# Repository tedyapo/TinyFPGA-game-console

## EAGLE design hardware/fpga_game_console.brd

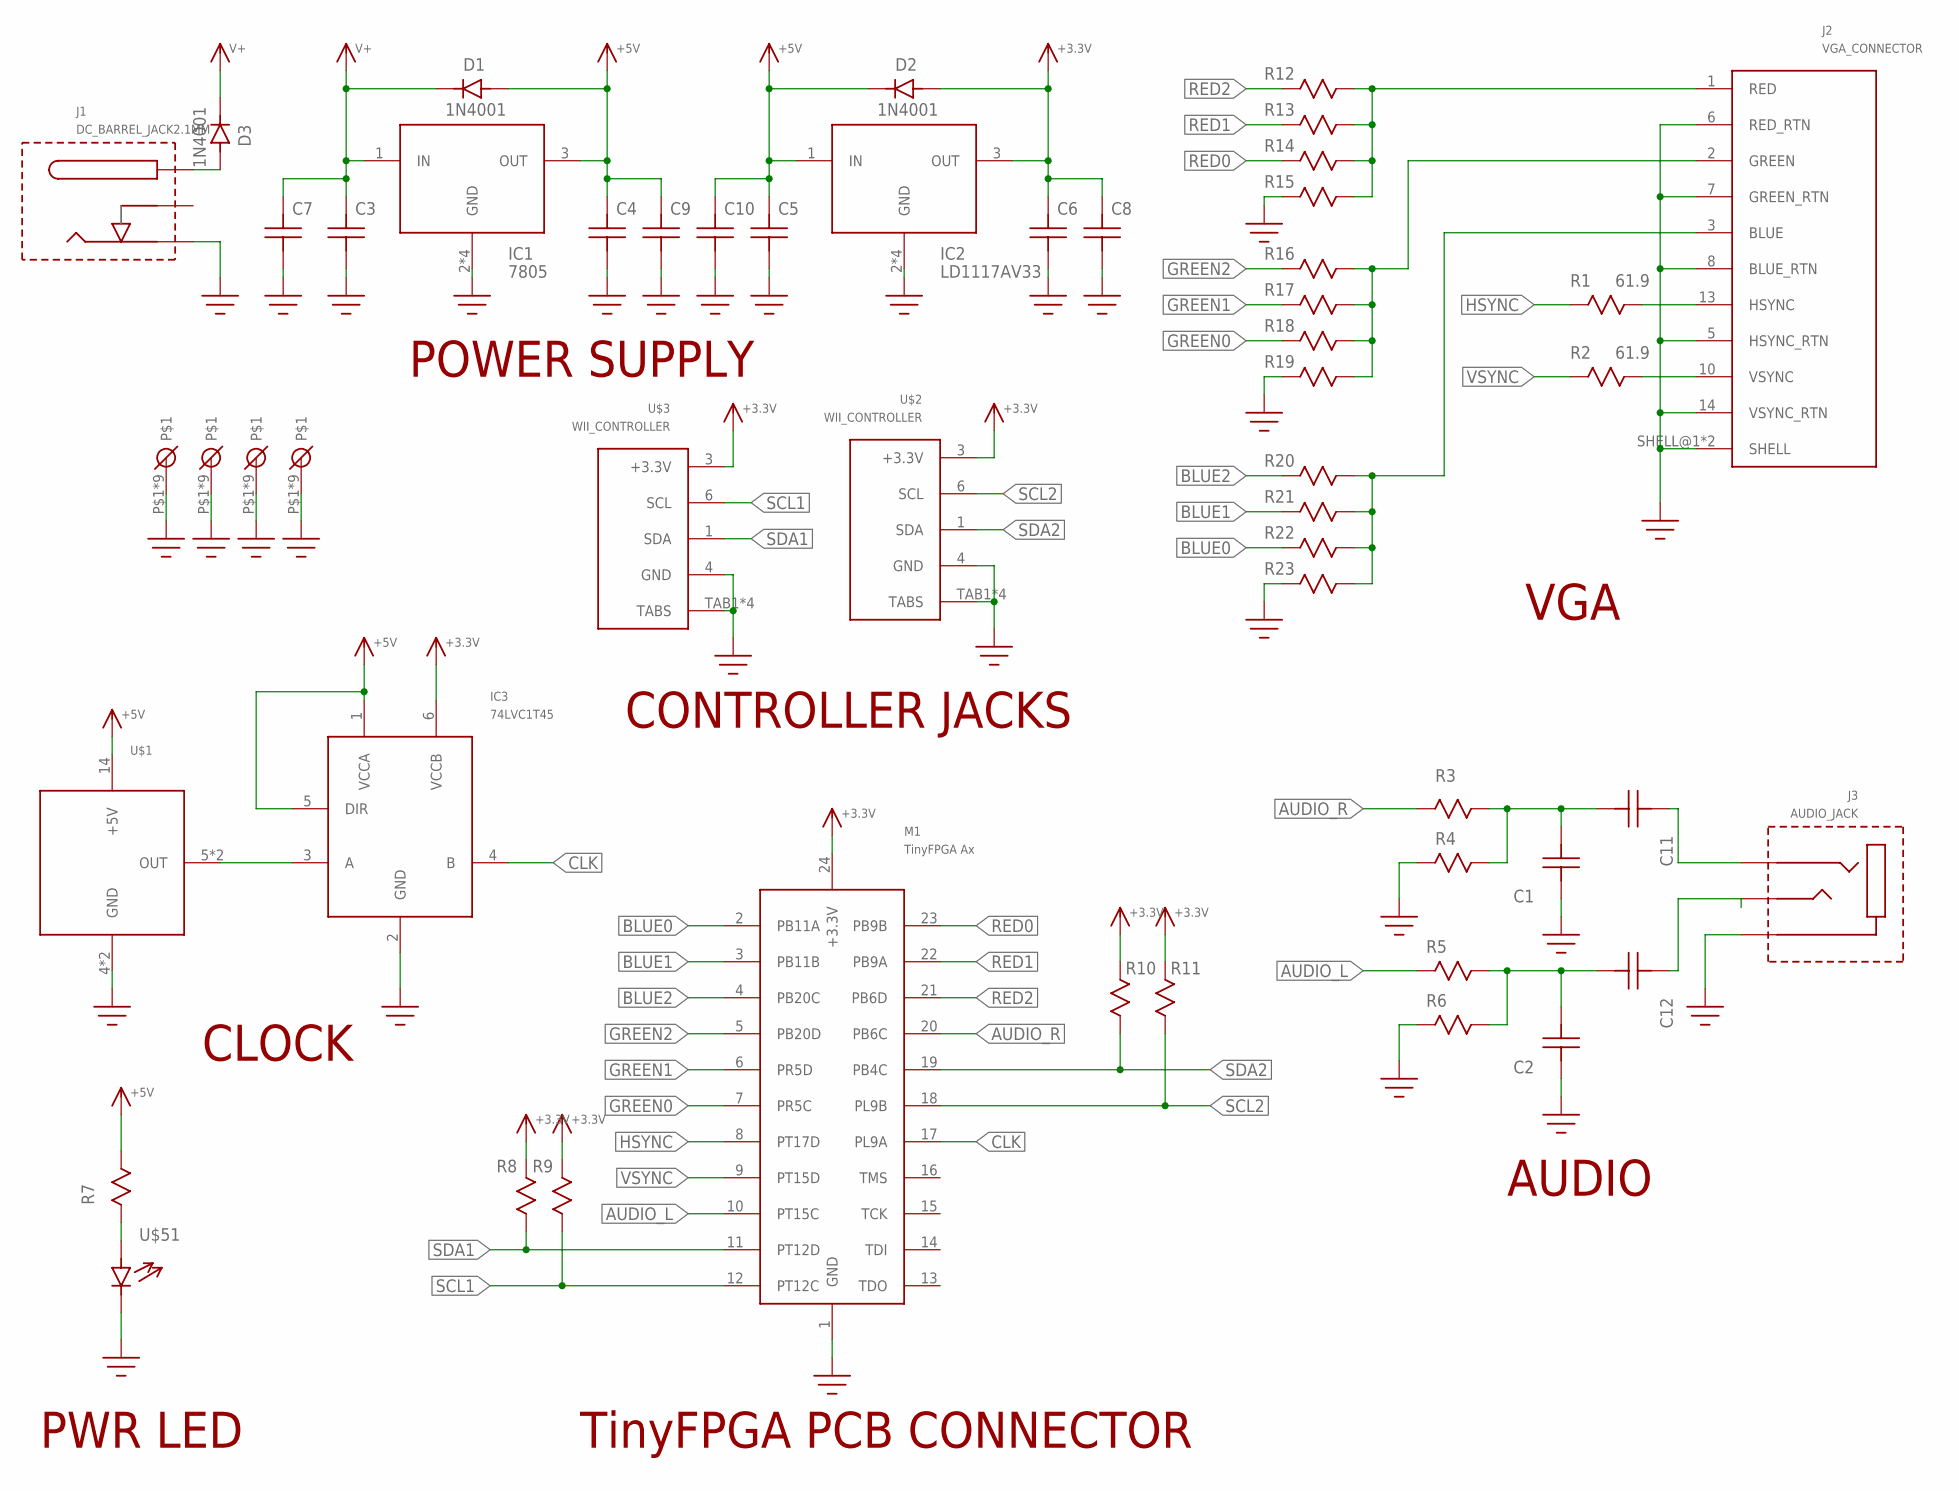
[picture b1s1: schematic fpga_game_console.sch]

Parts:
C1, C2, C3, C4, C5, C6, C7, C8, C9, C10, C11, C12: C; C50X100
D1, D2, D3: 1N4001; DO-41
IC1: 7805; TO-220
IC2: LD1117AV33; TO-220
IC3: 74LVC1T45; SOT23-6
J1: DC_BARREL_JACK2.1MM; 2.1MM_BARREL
J2: VGA_CONNECTOR; VGA_CONNECTOR_FCI
J3: AUDIO_JACK; 3.5MM_AUDIO_JACK
M1: TinyFPGA Ax; TINYFPGA_A
R1, R2: 61.9; R_0.25W
R3, R4, R5, R6, R7, R8, R9, R10, R11, R12, R13, R14, R15, R16, R17, R18, R19, R20, R21, R22, R23: R; R_0.25W
U$1: DUAL_OSCILLATOR; DUAL_OSC_CAN
U$2, U$3: WII_CONTROLLER; WII_CONNECTOR
U$51: LED; LED_5MM_RA
U$55, U$56, U$57, U$58: MOUNTING_HOLE; 4-40_MOUNTING_HOLE_SMALL_OUTLINE

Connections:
+3.3V: C6.P$2, C8.P$2, D2.A, IC2.3 (OUT), IC3.6 (VCCB), M1.24 (+3.3V), R8.P$2, R9.P$2, R10.P$2, R11.P$2, U$2.3 (+3.3V), U$3.3 (+3.3V)
+5V: C4.P$2, C5.P$2, C9.P$2, C10.P$2, D1.A, D2.C, IC1.3 (OUT), IC2.1 (IN), IC3.1 (VCCA), IC3.5 (DIR), R7.P$1, U$1.14 (+5V)
AUDIO_L: M1.10 (PT15C), R5.P$2
AUDIO_R: M1.20 (PB6C), R3.P$2
BLUE0: M1.2 (PB11A), R22.P$2
BLUE1: M1.3 (PB11B), R21.P$2
BLUE2: M1.4 (PB20C), R20.P$2
CLK: IC3.4 (B), M1.17 (PL9A)
GND: C1.P$2, C2.P$2, C3.P$1, C4.P$1, C5.P$1, C6.P$1, C7.P$1, C8.P$1, C9.P$1, C10.P$1, IC1.2 (GND), IC1.HS@1 (GND), IC1.HS@2 (GND), IC1.HS@3 (GND), IC2.2 (GND), IC2.HS@1 (GND), IC2.HS@2 (GND), IC2.HS@3 (GND), IC3.2 (GND), J1.2, J2.5 (HSYNC_RTN), J2.6 (RED_RTN), J2.7 (GREEN_RTN), J2.8 (BLUE_RTN), J2.14 (VSYNC_RTN), J2.SHELL@1 (SHELL), J2.SHELL@2 (SHELL), J3.1, M1.1 (GND), R4.P$2, R6.P$2, R15.P$2, R19.P$2, R23.P$2, U$1.4 (GND), U$1.7 (GND), U$2.4 (GND), U$2.TAB1 (TABS), U$2.TAB2 (TABS), U$2.TAB3 (TABS), U$2.TAB4 (TABS), U$3.4 (GND), U$3.TAB1 (TABS), U$3.TAB2 (TABS), U$3.TAB3 (TABS), U$3.TAB4 (TABS), U$51.C, U$55.P$1, U$55.P$2, U$55.P$3, U$55.P$4, U$55.P$5, U$55.P$6, U$55.P$7, U$55.P$8, U$55.P$9, U$56.P$1, U$56.P$2, U$56.P$3, U$56.P$4, U$56.P$5, U$56.P$6, U$56.P$7, U$56.P$8, U$56.P$9, U$57.P$1, U$57.P$2, U$57.P$3, U$57.P$4, U$57.P$5, U$57.P$6, U$57.P$7, U$57.P$8, U$57.P$9, U$58.P$1, U$58.P$2, U$58.P$3, U$58.P$4, U$58.P$5, U$58.P$6, U$58.P$7, U$58.P$8, U$58.P$9
GREEN0: M1.7 (PR5C), R18.P$2
GREEN1: M1.6 (PR5D), R17.P$2
GREEN2: M1.5 (PB20D), R16.P$2
HSYNC: M1.8 (PT17D), R1.P$1
unnamed: D3.A, J1.1
unnamed: IC3.3 (A), U$1.5 (OUT), U$1.8 (OUT)
unnamed: J2.1 (RED), R12.P$2, R13.P$2, R14.P$2, R15.P$1
unnamed: J2.2 (GREEN), R16.P$1, R17.P$1, R18.P$1, R19.P$1
unnamed: J2.3 (BLUE), R20.P$1, R21.P$1, R22.P$1, R23.P$1
unnamed: C1.P$1, C11.P$1, R3.P$1, R4.P$1
unnamed: C2.P$1, C12.P$1, R5.P$1, R6.P$1
unnamed: R7.P$2, U$51.A
unnamed: C11.P$2, J3.3
unnamed: J2.13 (HSYNC), R1.P$2
unnamed: J2.10 (VSYNC), R2.P$2
RED0: M1.23 (PB9B), R14.P$1
RED1: M1.22 (PB9A), R13.P$1
RED2: M1.21 (PB6D), R12.P$1
SCL1: M1.12 (PT12C), R9.P$1, U$3.6 (SCL)
SCL2: M1.18 (PL9B), R11.P$1, U$2.6 (SCL)
SDA1: M1.11 (PT12D), R8.P$1, U$3.1 (SDA)
SDA2: M1.19 (PB4C), R10.P$1, U$2.1 (SDA)
V+: C3.P$2, C7.P$2, D1.C, D3.C, IC1.1 (IN)
VSYNC: M1.9 (PT15D), R2.P$1

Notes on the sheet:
VGA
AUDIO
POWER SUPPLY
CLOCK
TinyFPGA PCB CONNECTOR
PWR LED
CONTROLLER JACKS

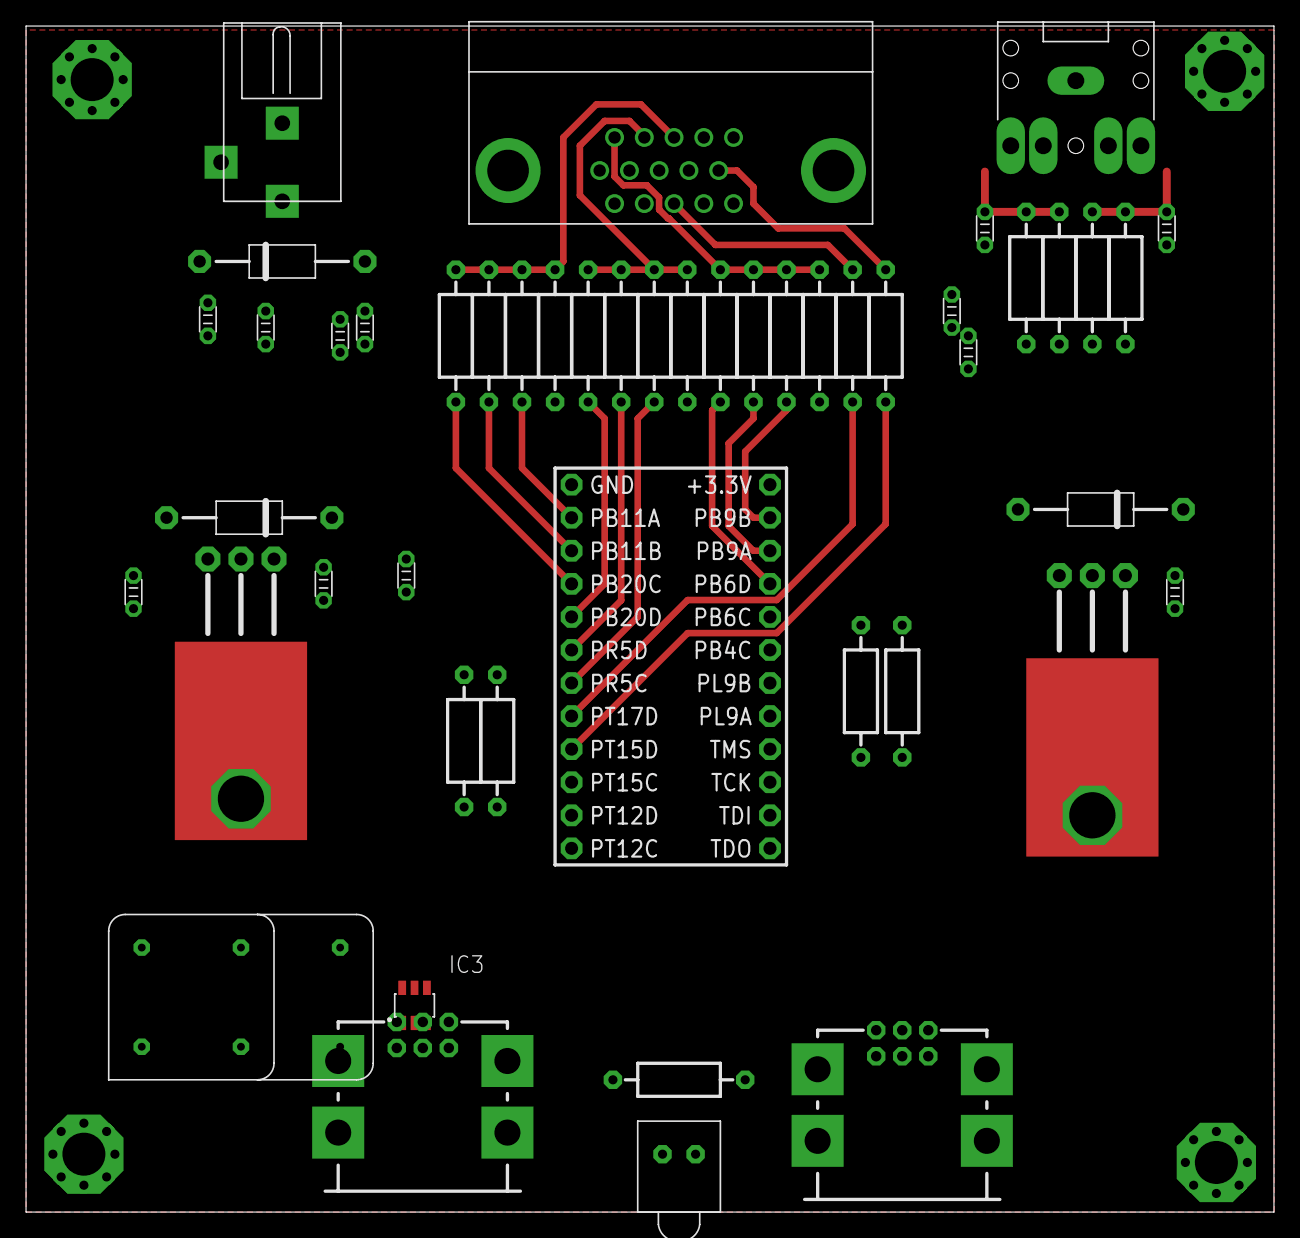
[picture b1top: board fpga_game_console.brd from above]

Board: 2 copper layers, 95.9 x 91.1 mm, 53 parts (0 on the bottom side), 33 nets.

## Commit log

2018-02-14 first checkin
